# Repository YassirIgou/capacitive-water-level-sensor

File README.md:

# Capacitive Water-Level Monitoring System

**A prototype for measuring water level using capacitive sensing, analog signal conditioning, and an STM32 microcontroller.**

## Overview

This academic project, carried out at **Mines Saint-Étienne (ISMIN)**, explores a non-mechanical method for monitoring the level of water in a container. Two insulated electrodes form a capacitor whose capacitance changes as the water level rises or falls. An analog conditioning circuit converts the small capacitance variation into a measurable oscillating signal. An **STM32F301K8** measures its period, estimates the water level using experimental calibration, and provides local display and Bluetooth communication.

The documented prototype integrates:

- **Capacitive sensing:** two electrically insulated electrodes immersed in water.
- **Analog electronics:** a constant-current-based conditioning circuit and hysteresis comparator, producing an oscillating signal.
- **Embedded acquisition:** STM32 timer input capture to measure the signal period.
- **Calibration:** an experimentally determined relationship between capacitance and water height.
- **User interface:** an OLED screen and Bluetooth commands/low-level alerts.

The full project report is available in **[docs/Rapport_Projet.pdf](docs/Rapport_Projet.pdf)** (in French).

## System architecture

```mermaid
flowchart LR
    A[Insulated capacitor electrodes] -->|Capacitance varies with water level| B[Analog signal conditioner]
    B -->|Oscillating signal| C[STM32F301K8<br/>TIM2 input capture]
    C --> D[Period / capacitance calculation]
    D --> E[Experimental calibration<br/>water-level estimation]
    E --> F[OLED display]
    E --> G[Bluetooth interface<br/>queries and low-level alerts]
```

### Operating principle

1. **Water-level change:** as the immersed portion of the electrodes changes, the dielectric distribution between the electrodes changes, and so does capacitance.
2. **Capacitance-to-period conversion:** the conditioning circuit uses a current source and a hysteresis comparator to generate an oscillating signal related to the sensor capacitance.
3. **Digital acquisition:** TIM2 on the STM32 is configured in **Input Capture** mode. The interval between two captured rising edges is used to determine signal period.
4. **Level estimation:** an experimental calibration curve converts the measured signal into an estimated water height.
5. **Output:** the estimated level is displayed on the OLED; Bluetooth supports commands and an automatic alert when the level falls below a configured threshold.

## Hardware and tools

| Area | Hardware / software | Role in the project |
| --- | --- | --- |
| Sensor | Two insulated electrodes | Capacitive detection of immersion height |
| Analog electronics | Constant-current conversion and hysteresis comparator | Capacitance-dependent oscillator |
| Embedded system | **STM32F301K8**, **STM32CubeIDE** | Timer capture, signal processing and peripheral control |
| Electronics design | **KiCad** | KiCad schematics and PCB layout design |
| Multiphysics simulation | **COMSOL Multiphysics** | Electrostatic modeling of capacitance versus water height |
| Measurements | **WaveForms** | Observation of conditioning-circuit signals |
| User interface | **OLED** and **Bluetooth** module | Local measurement display, remote requests and alerts |
| Mechanical design | **Autodesk Inventor**, 3D printing | Electrode support / mechanical prototyping |

## Repository Structure

```text
capacitive-water-level-sensor/
│
├── docs/
│   └── Rapport_Projet.pdf      # Complete technical report
│
├── firmware/
│   └── stm32/                  # STM32CubeIDE project and C source code
│
├── hardware/
│   └── kicad/                  # KiCad schematics and PCB design
│
├── simulation/
│   └── comsol/                 # COMSOL models
│
├── mechanical/
│   └── electrode_support.ipt   # Autodesk Inventor 3D CAD model
│
└── README.md                   # Project documentation
```

## Project team

- **Mohamed Yassir IGOUZOULENE**
- **Imane MOUMOUN**

## Documentation

- **[Full project report (PDF, French)](docs/Rapport_Projet.pdf)**

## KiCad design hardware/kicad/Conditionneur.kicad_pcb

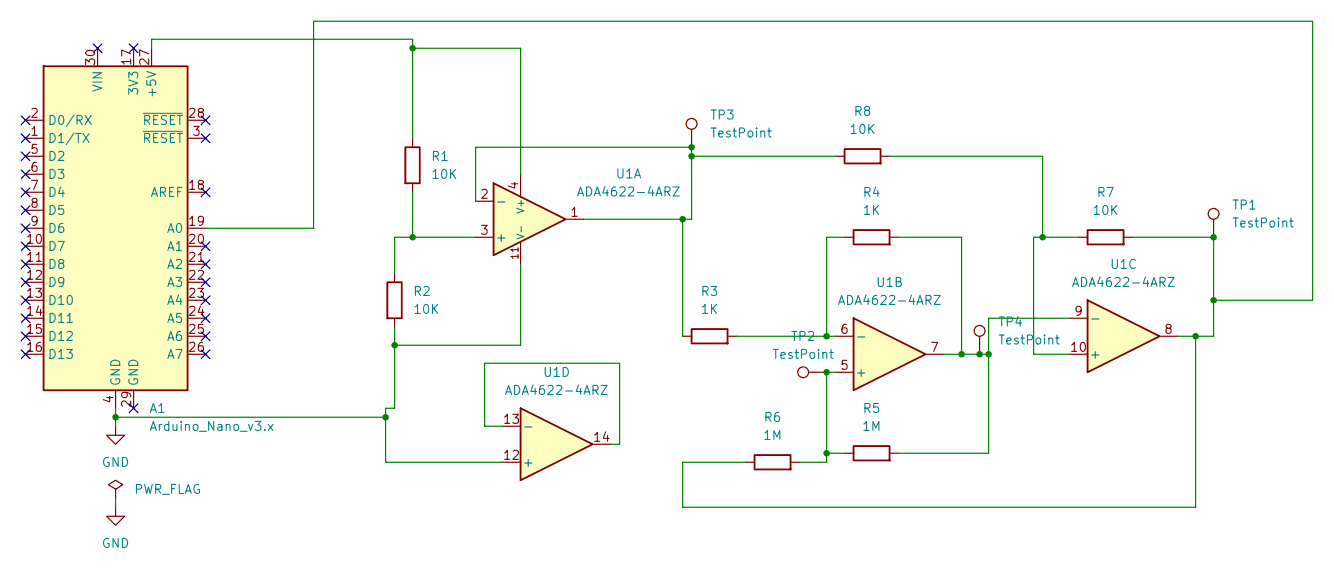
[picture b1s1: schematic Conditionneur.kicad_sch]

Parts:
A1: Arduino_Nano_v3.x; Arduino_Nano
R1, R2, R7, R8: 10K; R_0805_2012Metric_Pad1.20x1.40mm_HandSolder
R3, R4: 1K; R_0805_2012Metric_Pad1.20x1.40mm_HandSolder
R5, R6: 1M; R_0805_2012Metric_Pad1.20x1.40mm_HandSolder
TP1, TP2, TP3, TP4: TestPoint; PinHeader_1x01_P1.00mm_Vertical
U1: ADA4622-4ARZ; SOIC-14_3.9x8.7mm_P1.27mm

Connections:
GND: A1.4 (GND), R2.2, U1.11 (V-), U1.12 (+)
unnamed: A1.27 (+5V), R1.1, U1.4 (V+)
unnamed: A1.19 (A0), R6.1, R7.2, TP1.1, U1.8
unnamed: R1.2, R2.1, U1.3 (+)
unnamed: R3.1, R8.1, TP3.1, U1.1, U1.2 (-)
unnamed: R5.1, R6.2, TP2.1, U1.5 (+)
unnamed: R3.2, R4.1, U1.6 (-)
unnamed: R7.1, R8.2, U1.10 (+)
unnamed: R4.2, R5.2, TP4.1, U1.7, U1.9 (-)
unnamed: U1.13 (-), U1.14

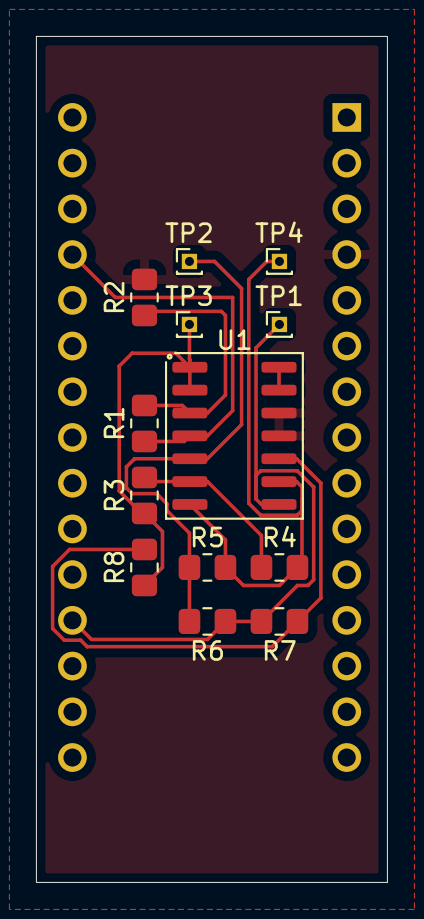
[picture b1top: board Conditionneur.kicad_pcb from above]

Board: 2 copper layers, 19.5 x 47.0 mm, 14 parts (1 on the bottom side), 10 nets.
